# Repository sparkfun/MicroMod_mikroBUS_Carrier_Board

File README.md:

MicroMod mikroBUS™ Carrier Board
========================================

[*SparkFun MicroMod mikroBUS™ Carrier Board (DEV-18710)*](https://www.sparkfun.com/products/18710)

The SparkFun MicroMod mikroBUS Carrier Board takes advantage of the [MicroMod](https://www.sparkfun.com/micromod), [Qwiic](https://www.sparkfun.com/qwiic), and [mikroBUS™](https://www.mikroe.com/mikrobus) ecosystems and allows users to take advantage of the growing number of 7 [MicroMod processor boards](https://www.sparkfun.com/categories/tags/processor-board), 83 [Qwiic *(add-on)* boards](https://www.sparkfun.com/categories/tags/qwiic), and [1079 available](https://www.mikroe.com/click-boards) [Click boards™](https://www.sparkfun.com/categories/tags/click) *(as of September 2021)*, which equates to +51M different board combinations.

The mikroBUS socket comprises a pair of 8-pin female headers with a standardized pin configuration. The pins consist of three groups of communications pins (SPI, UART and I<sup>2</sup>C), six additional pins (PWM, Interrupt, Analog input, Reset and Chip select), and two power groups (3.3V and 5V).

_The [mikroBUS™ standard](https://www.mikroe.com/mikrobus) was developed by [MikroElektronika](https://www.mikroe.com/). Similar to our [Qwiic](https://www.sparkfun.com/qwiic) and [MicroMod](https://www.sparkfun.com/micromod) interfaces, mikroBUS™ provides a standardized connection for add-on [Click boards™](https://www.mikroe.com/click-boards) to be hooked up to a microcontroller based development board._

Repository Contents
-------------------

* **/Documentation** - Data sheets, additional product information
* **/Hardware** - Eagle design files (.brd, .sch)

Documentation
--------------

* **[Hookup Guide](https://learn.sparkfun.com/tutorials/2003)** - SparkFun MicroMod mikroBUS™ Carrier Board

Product Versions
----------------
* [DEV-18710](https://www.sparkfun.com/products/18710) -  initial release

License Information
-------------------

This product is _**open source**_! 

Please review the LICENSE.md file for license information. 

If you have any questions or concerns on licensing, please contact technical support on our [SparkFun forums](https://forum.sparkfun.com/viewforum.php?f=152).

Distributed as-is; no warranty is given.

- Your friends at SparkFun.

_<COLLABORATION CREDIT>_

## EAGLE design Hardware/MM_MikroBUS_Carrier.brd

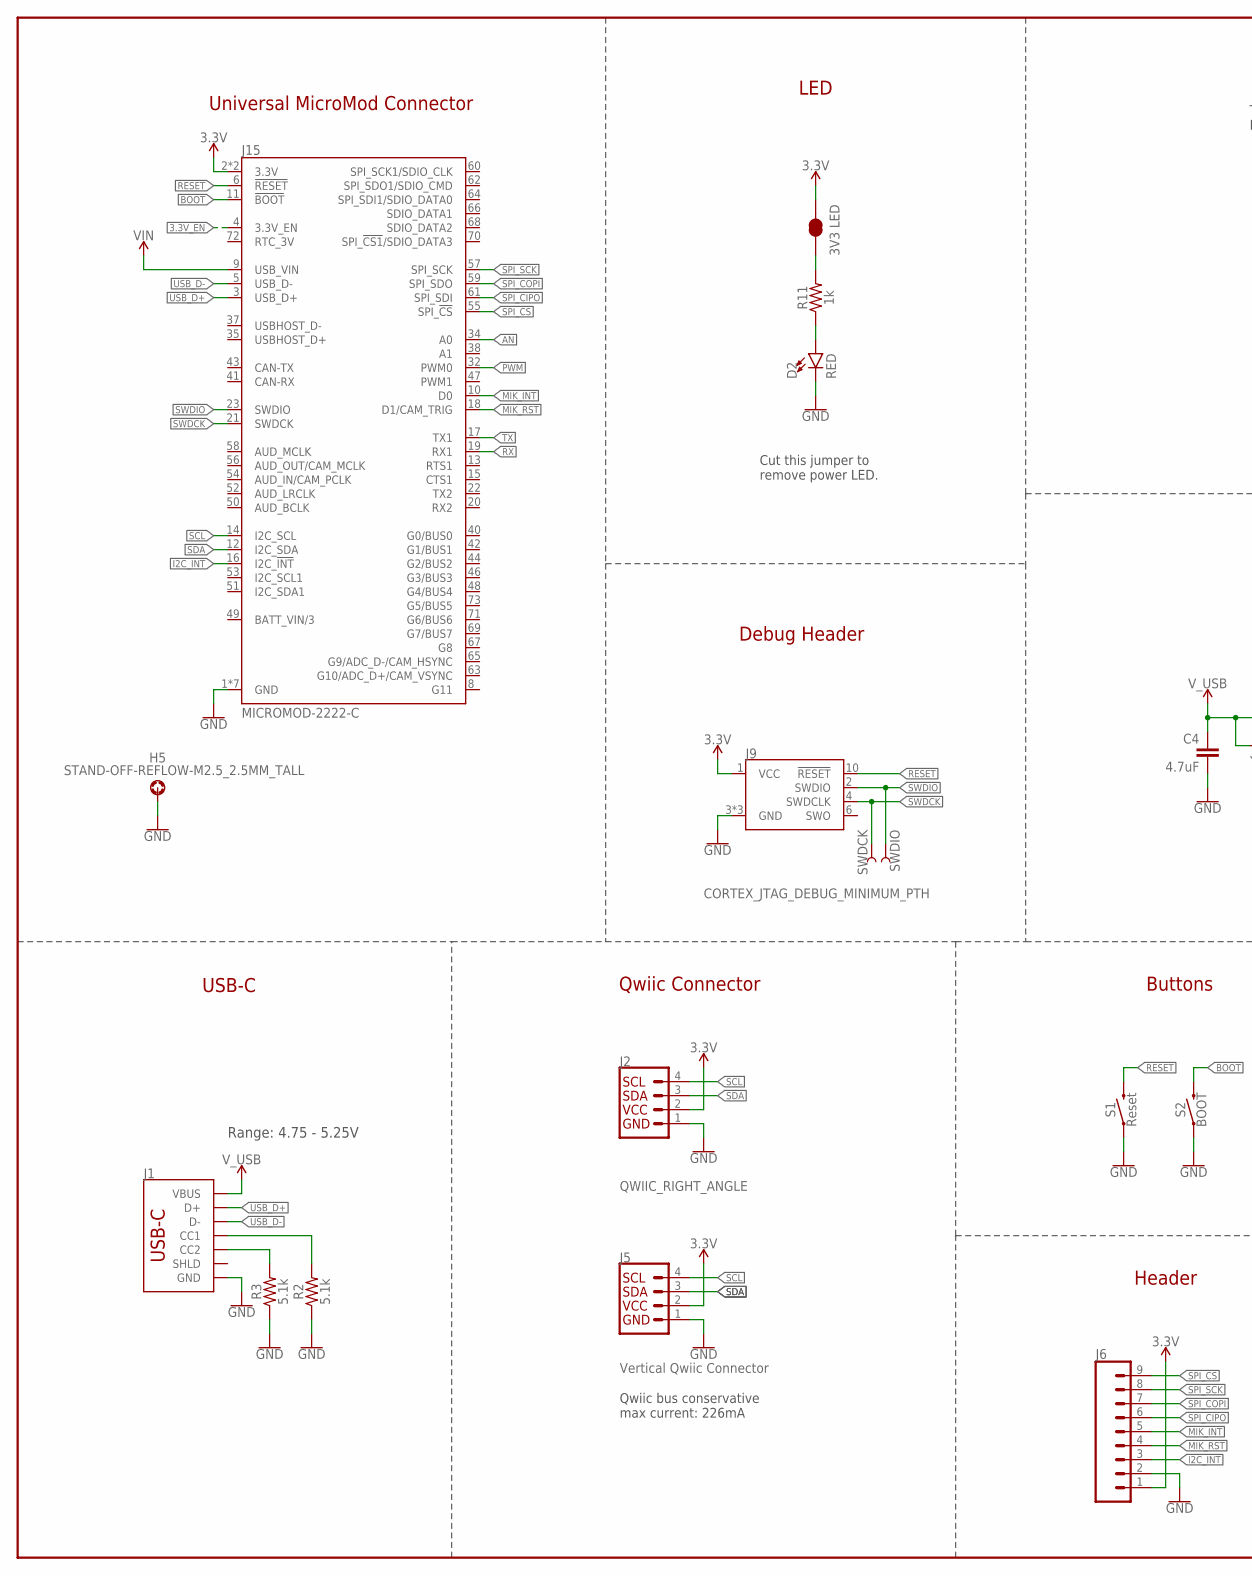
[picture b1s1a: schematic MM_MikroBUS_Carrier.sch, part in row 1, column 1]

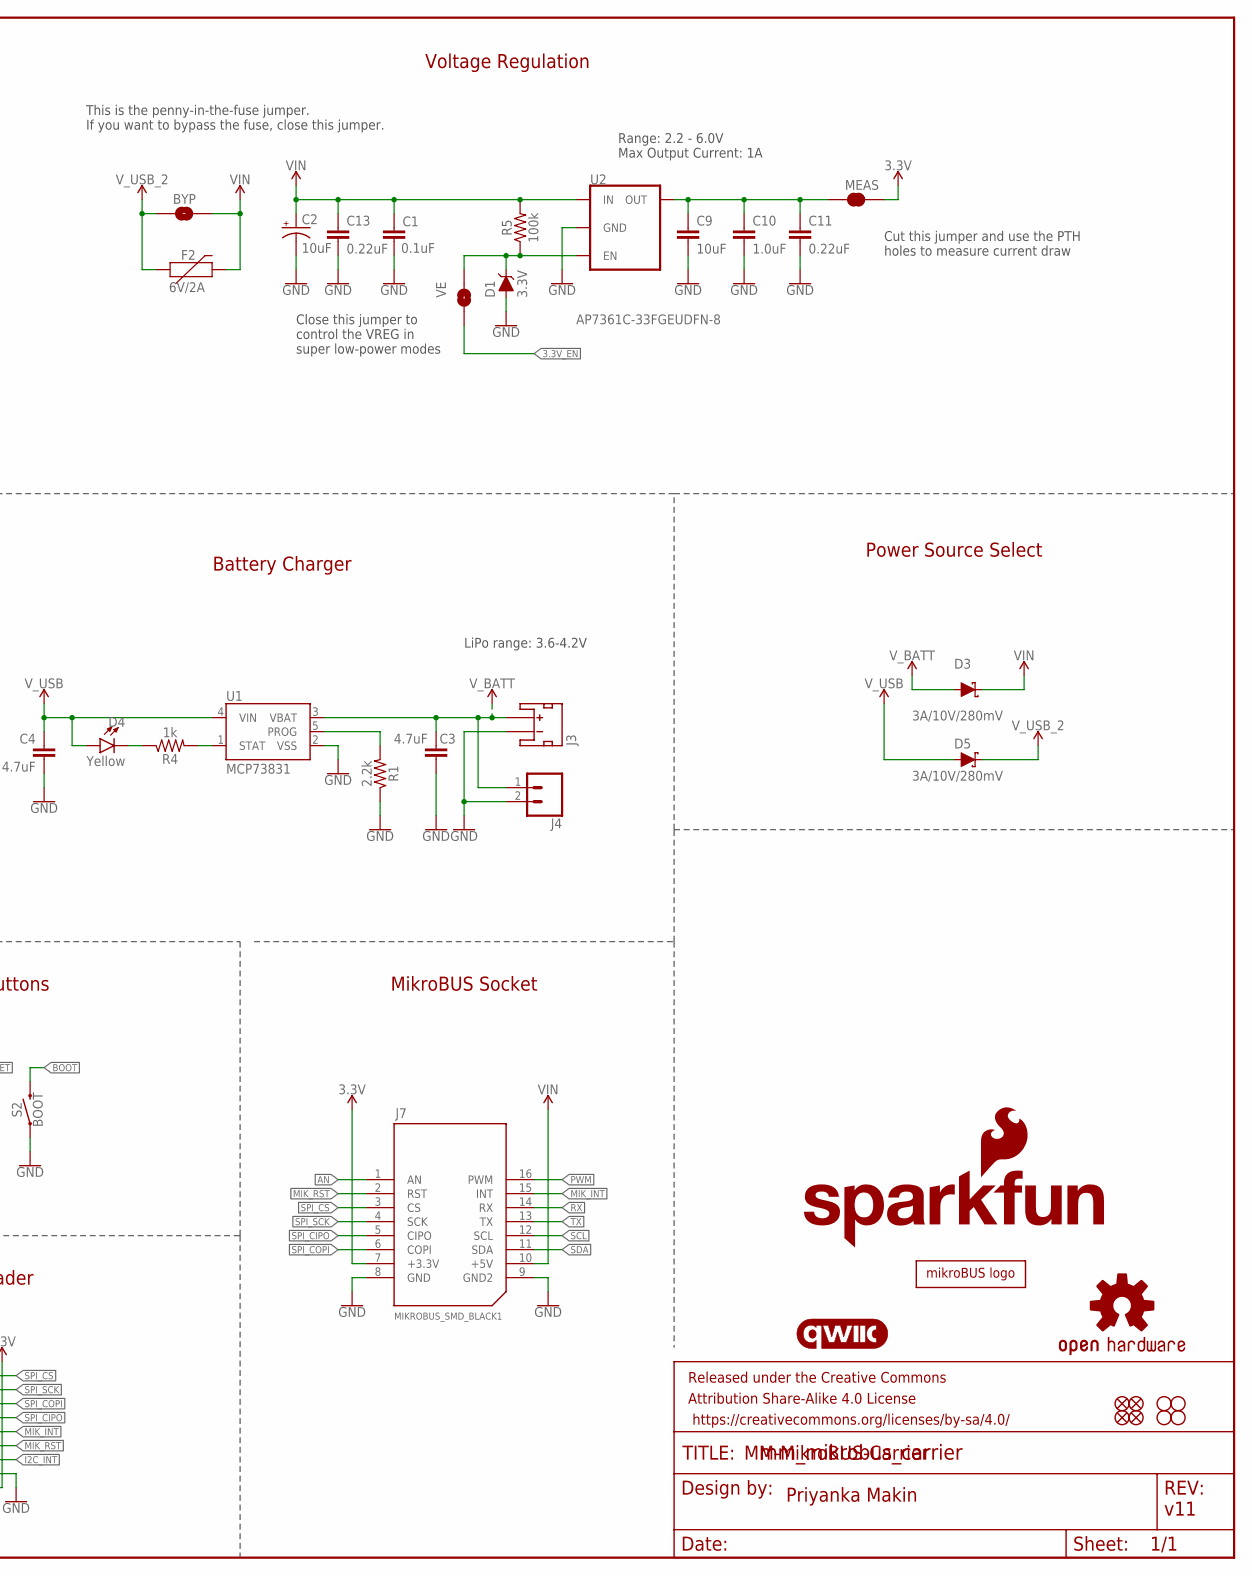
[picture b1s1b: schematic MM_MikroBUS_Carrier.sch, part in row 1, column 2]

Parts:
BYP: JUMPER-SMT_2_NO_SILK; SMT-JUMPER_2_NO_SILK
C1: 0.1uF; 0603
C2: 10uF; EIA3216
C3, C4: 4.7uF; 0603
C9: 10uF; 0603
C10: 1.0uF; 0603
C11, C13: 0.22uF; 0603
D1: 3.3V; SOD-323
D2: RED; LED-0603
D3, D5: 3A/10V/280mV; SOD-323
D4: Yellow; LED-0603
F2: 6V/2A; 1210
FD1, FD2, FD3, FD4: FIDUCIALUFIDUCIAL; FIDUCIAL-MICRO
FRAME1: FRAME-LEDGER; CREATIVE_COMMONS
H1, H2, H3, H4: STAND-OFF
H5: STAND-OFF-REFLOW-M2.5_2.5MM_TALL; STAND-OFF-REFLOW-M2.5
J1: USB_C_2-LAYER_PADS; USB-C-16P-2LAYER-PADS
J2: QWIIC_RIGHT_ANGLE; JST04_1MM_RA
J3: JST_2MM_MALE; JST-2-SMD
J4: CONN_021X02_NO_SILK; 1X02_NO_SILK
J5: Vertical Qwiic Connector; JST04_1MM_VERT
J6: CONN_09NO_SILK; 1X09_NO_SILK
J7: MIKROBUS_SMD_BLACK1; MIKROBUS_SMD_BLACK
J9: CORTEX_JTAG_DEBUG_MINIMUM_PTH; 2X5-PTH-1.27MM
J15: MICROMOD-2222-C; M.2-CONNECTOR-E
JP4: 3V3 LED; SMT-JUMPER_2_NC_TRACE_SILK
JP6: VE; SMT-JUMPER_2_NO_SILK
LOGO1: SFE_LOGO_NAME_FLAME.2_INCH; SFE_LOGO_NAME_FLAME_.2
LOGO2: QWIIC_LOGO_CONNECTOR; QWIIC_5.5MM
LOGO3: OSHW-LOGOM; OSHW-LOGO-M
MEAS: JUMPER-COMBO_2_NC_TRACE; COMBO-JUMPER_2_NC_TRACE
R1: 2.2k; 0603
R2, R3: 5.1k; 0603
R4, R11: 1k; 0603
R5: 100k; 0603
S1: Reset; TACTILE_SWITCH_SMD_5.2MM
S2: BOOT; TACTILE_SWITCH_SMD_5.2MM
SWDCK: TEST-POINTTP_15TH_THRU; TP_15TH
SWDIO: TEST-POINTTP_15TH_THRU; TP_15TH
U1: MCP73831; SOT23-5
U2: AP7361C-33FGEUDFN-8; UDFN-8
U$7: MIKROBUS_LOGO

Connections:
3.3V: J2.2, J5.2, J6.1, J7.7 (+3.3V), J9.1 (VCC), J15.2 (3.3V), J15.74 (3.3V), JP4.2, MEAS.2, MEAS.4 (2)
3.3V_EN: J15.4 (3.3V_EN), JP6.1
!BOOT!: J15.11 (!BOOT!), S2.3 (2), S2.4 (2)
!RESET!: J9.10 (!RESET), J15.6 (!RESET!), S1.3 (2), S1.4 (2)
AN: J7.1 (AN), J15.34 (A0)
GND: C1.2, C2.-, C3.2, C4.2, C9.2, C10.2, C11.2, C13.2, D1.A, D2.C, H5.1, J1.GND, J1.GND2 (GND), J2.1, J3.1 (-), J4.2, J5.1, J6.2, J7.8 (GND), J7.9 (GND2), J9.3 (GND), J9.5 (GND), J9.9 (GND), J15.1 (GND), J15.7 (GND), J15.33 (GND), J15.36 (GND), J15.39 (GND), J15.45 (GND), J15.75 (GND), R1.1, R2.1, R3.1, S1.1, S1.2 (1), S2.1, S2.2 (1), U1.2 (VSS), U2.4 (GND), U2.EP (GND)
I2C_!INT!: J6.3, J15.16 (I2C_!INT!)
MIK_INT: J6.5, J7.15 (INT), J15.10 (D0)
MIK_RST: J6.4, J7.2 (RST), J15.18 (D1/CAM_TRIG)
unnamed: C9.1, C10.1, C11.1, MEAS.1, MEAS.3 (1), U2.1 (OUT)
unnamed: R1.2, U1.5 (PROG)
unnamed: D4.C, R4.1
unnamed: JP4.1, R11.2
unnamed: D2.A, R11.1
unnamed: R4.2, U1.1 (STAT)
unnamed: J1.A5 (CC1), R2.2
unnamed: J1.B5 (CC2), R3.2
PWM: J7.16 (PWM), J15.32 (PWM0)
RX: J7.14 (RX), J15.19 (RX1)
SCL: J2.4, J5.4, J7.12 (SCL), J15.14 (I2C_SCL)
SDA: J2.3, J5.3, J7.11 (SDA), J15.12 (I2C_SDA)
SPI_!CS!: J6.9, J7.3 (CS), J15.55 (SPI_!CS!)
SPI_CIPO: J6.6, J7.5 (CIPO), J15.61 (SPI_SDI)
SPI_COPI: J6.7, J7.6 (COPI), J15.59 (SPI_SDO)
SPI_SCK: J6.8, J7.4 (SCK), J15.57 (SPI_SCK)
SWDCK: J9.4 (SWDCLK), J15.21 (SWDCK), SWDCK.1
SWDIO: J9.2 (SWDIO), J15.23 (SWDIO), SWDIO.1
TX: J7.13 (TX), J15.17 (TX1)
USB_D+: J1.A6 (D+), J1.B6 (D+), J15.3 (USB_D+)
USB_D-: J1.A7 (D-), J1.B7 (D-), J15.5 (USB_D-)
VIN: BYP.2, C1.1, C2.+, C13.1, D3.C, F2.2, J7.10 (+5V), J15.9 (USB_VIN), R5.2, U2.8 (IN)
VREG_EN: D1.C, JP6.2, R5.1, U2.5 (EN)
V_BATT: C3.1, D3.A, J3.2 (+), J4.1, U1.3 (VBAT)
V_USB: C4.1, D4.A, D5.A, J1.VBUS1 (VBUS), J1.VBUS2 (VBUS), U1.4 (VIN)
V_USB_2: BYP.1, D5.C, F2.1

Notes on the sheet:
USB-C
Universal MicroMod Connector
Priyanka Makin
MM-MikroBUS-Carrier
LED
v11
Cut this jumper to remove power LED.
Range: 4.75 - 5.25V
Voltage Regulation
Range: 2.2 - 6.0V Max Output Current: 1A
Close this jumper to control the VREG in super low-power modes
This is the penny-in-the-fuse jumper. If you want to bypass the fuse, close this jumper.
Qwiic Connector
Buttons
Battery Charger
Power Source Select
Qwiic bus conservative max current: 226mA
Header
Cut this jumper and use the PTH holes to measure current draw
LiPo range: 3.6-4.2V
MikroBUS Socket
Debug Header

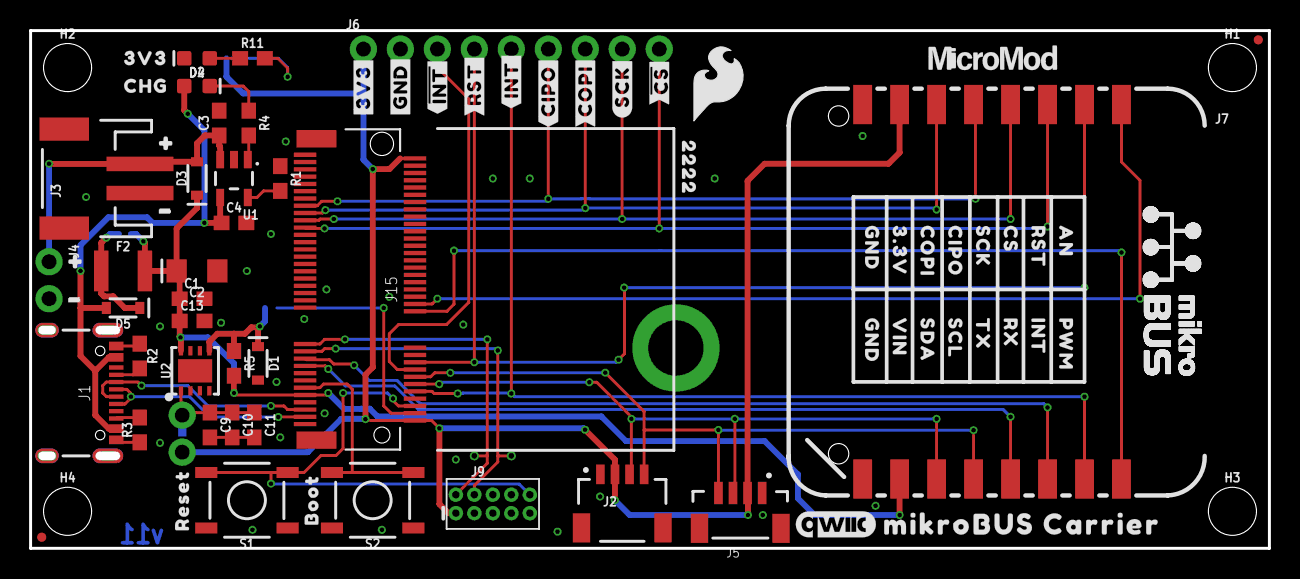
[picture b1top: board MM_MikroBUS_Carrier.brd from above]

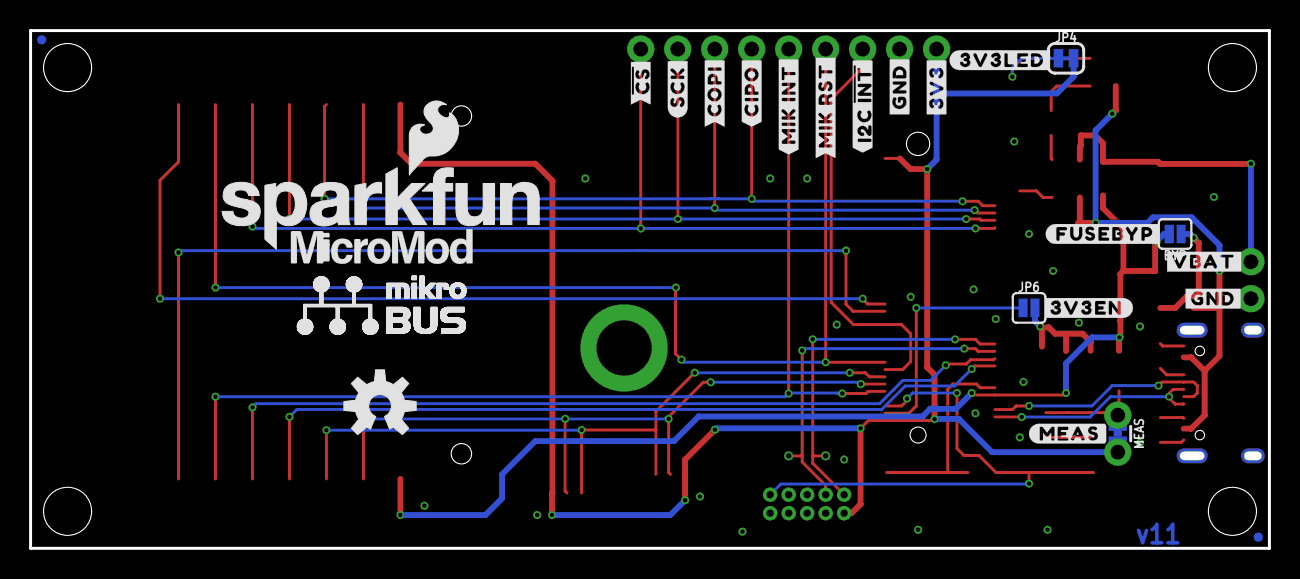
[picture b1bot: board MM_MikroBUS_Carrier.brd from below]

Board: 2 copper layers, 84.7 x 35.2 mm, 106 parts (25 on the bottom side), 35 nets.

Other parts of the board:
U$1: #3V3LED#0
U$2: MICROMOD_LOGO_.35
U$3: 3V30
U$4: CHG0
U$5: MIKROBUS_CARRIER0
U$6: #INT#0
U$8, U$14, U$33: #GND#0
U$9: #MEAS#0
U$10, U$13: #3V3#0
U$11, U$32, U$36, U$37: #0
U$12: #VBAT#0
U$15: ##INT##0
U$16: #MIK_INT#0
U$17: #RST#0
U$19: #MIK_RST#0
U$20: #I2C_#INT##0
U$22, U$23: #CIPO#0
U$24, U$25: #COPI#0
U$26, U$27: #SCK#0
U$28, U$29: ##CS##0
U$30: RESET0
U$31: BOOT0
U$34: 22220
U$35: AN0
U$38: #FUSEBYP#0
U$39: #3V3EN#0
U$40: RST0
U$41: CS0
U$42: SCK0
U$43: CIPO0
U$44: SFE_LOGO_FLAME_.2
U$45: COPI0
U$46: 3#3V0
U$47, U$48: GND0
U$49: PWM0
U$50: INT0
U$51: RX0
U$52: TX0
U$53: SCL0
U$54: SDA0
U$55: VIN0
U$68: MICROMOD_LOGO_.5

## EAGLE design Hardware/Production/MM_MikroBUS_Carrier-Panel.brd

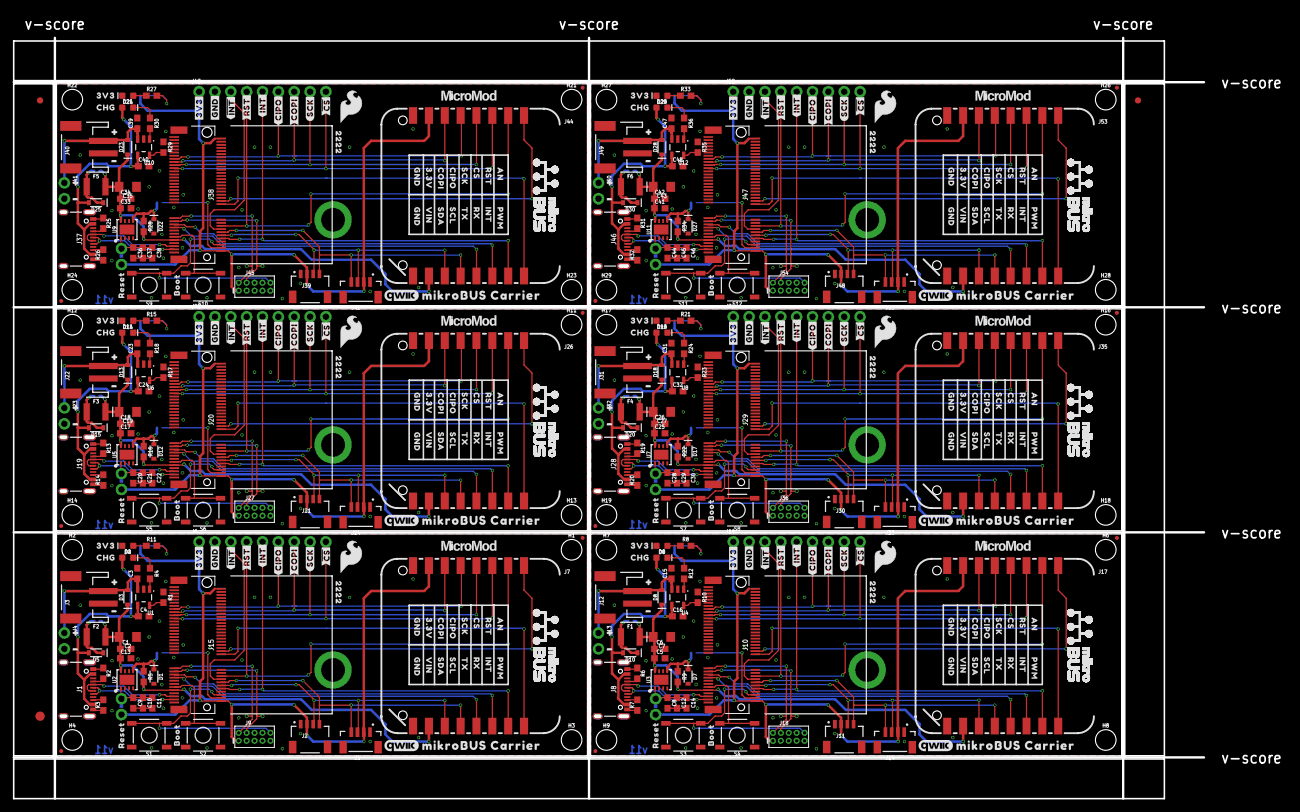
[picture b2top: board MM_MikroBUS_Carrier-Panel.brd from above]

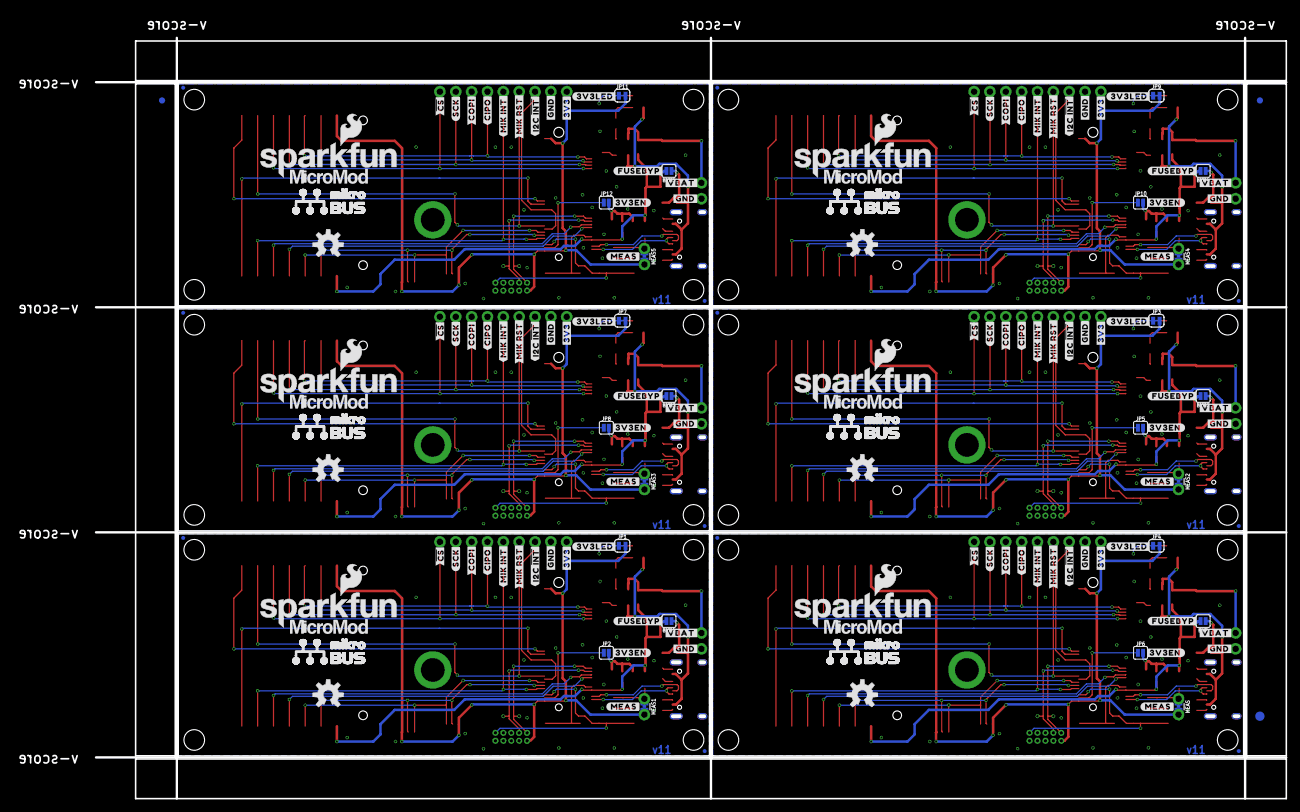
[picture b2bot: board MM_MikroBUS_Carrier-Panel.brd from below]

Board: 2 copper layers, 203.7 x 125.6 mm, 636 parts (153 on the bottom side), 210 nets.

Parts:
BYP, BYP1, BYP2, BYP3, BYP4, BYP5: JUMPER-SMT_2_NO_SILK; SMT-JUMPER_2_NO_SILK
C1, C6, C18, C26, C34, C42: 0.1uF; 0603
C2, C7, C19, C27, C35, C43: 10uF; EIA3216
C3, C4, C15, C16, C23, C24, C31, C32, C39, C40, C47, C48: 4.7uF; 0603
C5, C11, C13, C14, C17, C22, C25, C30, C33, C38, C41, C46: 0.22uF; 0603
C8, C9, C20, C28, C36, C44: 10uF; 0603
C10, C12, C21, C29, C37, C45: 1.0uF; 0603
D1, D7, D12, D17, D22, D27: 3.3V; SOD-323
D2, D6, D11, D16, D21, D26: RED; LED-0603
D3, D5, D8, D10, D13, D15, D18, D20, D23, D25, D28, D30: 3A/10V/280mV; SOD-323
D4, D9, D14, D19, D24, D29: Yellow; LED-0603
E$1, E$2, E$3, E$4: FIDUCIAL-1X2
E$5, E$6: FIDUCIAL-1.5X3
F1, F2, F3, F4, F5, F6: 6V/2A; 1210
FD1, FD2, FD3, FD4, FD5, FD6, FD7, FD8, FD9, FD10, FD11, FD12, FD13, FD14, FD15, FD16, FD17, FD18, FD19, FD20, FD21, FD22, FD23, FD24: FIDUCIALUFIDUCIAL; FIDUCIAL-MICRO
H1, H2, H3, H4, H6, H7, H8, H9, H11, H12, H13, H14, H16, H17, H18, H19, H21, H22, H23, H24, H26, H27, H28, H29: STAND-OFF
H5, H10, H15, H20, H25, H30: STAND-OFF-REFLOW-M2.5_2.5MM_TALL; STAND-OFF-REFLOW-M2.5
J1, J8, J19, J28, J37, J46: USB-C-16P-2LAYER-PADS
J2, J11, J21, J30, J39, J48: QWIIC_RIGHT_ANGLE; JST04_1MM_RA
J3, J12, J22, J31, J40, J49: JST-2-SMD
J4, J13, J23, J32, J41, J50: 1X02_NO_SILK
J5, J14, J24, J33, J42, J51: Vertical Qwiic Connector; JST04_1MM_VERT
J6, J16, J25, J34, J43, J52: 1X09_NO_SILK
J7, J17, J26, J35, J44, J53: MIKROBUS_SMD_BLACK1; MIKROBUS_SMD_BLACK
J9, J18, J27, J36, J45, J54: CORTEX_JTAG_DEBUG_MINIMUM_PTH; 2X5-PTH-1.27MM
J10, J15, J20, J29, J38, J47: MICROMOD-2222-C; M.2-CONNECTOR-E
JP1, JP3, JP4, JP7, JP9, JP11: 3V3 LED; SMT-JUMPER_2_NC_TRACE_SILK
JP2, JP5, JP6, JP8, JP10, JP12: VE; SMT-JUMPER_2_NO_SILK
LOGO1, LOGO6, LOGO9, LOGO12, LOGO15, LOGO18: SFE_LOGO_NAME_FLAME.2_INCH; SFE_LOGO_NAME_FLAME_.2
LOGO2, LOGO4, LOGO7, LOGO10, LOGO13, LOGO16: QWIIC_LOGO_CONNECTOR; QWIIC_5.5MM
LOGO3, LOGO5, LOGO8, LOGO11, LOGO14, LOGO17: OSHW-LOGOM; OSHW-LOGO-M
MEAS, MEAS1, MEAS2, MEAS3, MEAS4, MEAS5: JUMPER-COMBO_2_NC_TRACE; COMBO-JUMPER_2_NC_TRACE
R1, R10, R17, R23, R29, R35: 2.2k; 0603
R2, R3, R6, R7, R13, R14, R19, R20, R25, R26, R31, R32: 5.1k; 0603
R4, R8, R11, R12, R15, R18, R21, R24, R27, R30, R33, R36: 1k; 0603
R5, R9, R16, R22, R28, R34: 100k; 0603
S1, S3, S5, S7, S9, S11: Reset; TACTILE_SWITCH_SMD_5.2MM
S2, S4, S6, S8, S10, S12: BOOT; TACTILE_SWITCH_SMD_5.2MM
SWDCK, SWDCK1, SWDCK2, SWDCK3, SWDCK4, SWDCK5: TEST-POINTTP_15TH_THRU; TP_15TH
SWDIO, SWDIO1, SWDIO2, SWDIO3, SWDIO4, SWDIO5: TEST-POINTTP_15TH_THRU; TP_15TH
U1, U4, U6, U8, U10, U12: MCP73831; SOT23-5
U2, U3, U5, U7, U9, U11: AP7361C-33FGEUDFN-8; UDFN-8
U$1, U$100, U$154, U$208, U$262, U$316: #3V3LED#0
U$2, U$80, U$134, U$188, U$242, U$296: MICROMOD_LOGO_.35
U$3, U$58, U$113, U$167, U$221, U$275: 3V30
U$4, U$56, U$111, U$165, U$219, U$273: CHG0
U$5, U$83, U$137, U$191, U$245, U$299: MIKROBUS_CARRIER0
U$6, U$104, U$158, U$212, U$266, U$320: #INT#0
U$7, U$101, U$155, U$209, U$263, U$317: MIKROBUS_LOGO
U$8, U$14, U$33, U$59, U$60, U$69, U$114, U$115, U$123, U$168, U$169, U$177, U$222, U$223, U$231, U$276, U$277, U$285: #GND#0
U$9, U$57, U$112, U$166, U$220, U$274: #MEAS#0
U$10, U$13, U$81, U$82, U$135, U$136, U$189, U$190, U$243, U$244, U$297, U$298: #3V3#0
U$11, U$32, U$36, U$37, U$70, U$71, U$72, U$73, U$124, U$125, U$126, U$127, U$178, U$179, U$180, U$181, U$232, U$233, U$234, U$235, U$286, U$287, U$288, U$289: #0
U$12, U$67, U$122, U$176, U$230, U$284: #VBAT#0
U$15, U$79, U$133, U$187, U$241, U$295: ##INT##0
U$16, U$107, U$161, U$215, U$269, U$323: #MIK_INT#0
U$17, U$105, U$159, U$213, U$267, U$321: #RST#0
U$18, U$44, U$109, U$163, U$217, U$271: SFE_LOGO_FLAME_.2
U$19, U$108, U$162, U$216, U$270, U$324: #MIK_RST#0
U$20, U$106, U$160, U$214, U$268, U$322: #I2C_#INT##0
U$21, U$68, U$110, U$164, U$218, U$272: MICROMOD_LOGO_.5
U$22, U$23, U$61, U$62, U$116, U$117, U$170, U$171, U$224, U$225, U$278, U$279: #CIPO#0
U$24, U$25, U$63, U$64, U$118, U$119, U$172, U$173, U$226, U$227, U$280, U$281: #COPI#0
U$26, U$27, U$65, U$66, U$120, U$121, U$174, U$175, U$228, U$229, U$282, U$283: #SCK#0
U$28, U$29, U$77, U$78, U$131, U$132, U$185, U$186, U$239, U$240, U$293, U$294: ##CS##0
U$30, U$74, U$128, U$182, U$236, U$290: RESET0
U$31, U$75, U$129, U$183, U$237, U$291: BOOT0
U$34, U$76, U$130, U$184, U$238, U$292: 22220
U$35, U$84, U$138, U$192, U$246, U$300: AN0
U$38, U$102, U$156, U$210, U$264, U$318: #FUSEBYP#0
U$39, U$103, U$157, U$211, U$265, U$319: #3V3EN#0
U$40, U$85, U$139, U$193, U$247, U$301: RST0
U$41, U$86, U$140, U$194, U$248, U$302: CS0
U$42, U$87, U$141, U$195, U$249, U$303: SCK0
U$43, U$88, U$142, U$196, U$250, U$304: CIPO0
U$45, U$89, U$143, U$197, U$251, U$305: COPI0
U$46, U$90, U$144, U$198, U$252, U$306: 3#3V0
U$47, U$48, U$91, U$92, U$145, U$146, U$199, U$200, U$253, U$254, U$307, U$308: GND0
U$49, U$93, U$147, U$201, U$255, U$309: PWM0
U$50, U$94, U$148, U$202, U$256, U$310: INT0
U$51, U$95, U$149, U$203, U$257, U$311: RX0
U$52, U$96, U$150, U$204, U$258, U$312: TX0
U$53, U$97, U$151, U$205, U$259, U$313: SCL0
U$54, U$98, U$152, U$206, U$260, U$314: SDA0
U$55, U$99, U$153, U$207, U$261, U$315: VIN0

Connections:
3.3V: J2.2, J5.2, J6.1, J7.7, J9.1, J15.2, J15.74, JP4.2, MEAS.2, MEAS.4
3.3V1: J10.2, J10.74, J11.2, J14.2, J16.1, J17.7, J18.1, JP1.2, MEAS1.2, MEAS1.4
3.3V2: J20.2, J20.74, J21.2, J24.2, J25.1, J26.7, J27.1, JP3.2, MEAS2.2, MEAS2.4
3.3V3: J29.2, J29.74, J30.2, J33.2, J34.1, J35.7, J36.1, JP7.2, MEAS3.2, MEAS3.4
3.3V4: J38.2, J38.74, J39.2, J42.2, J43.1, J44.7, J45.1, JP9.2, MEAS4.2, MEAS4.4
3.3V5: J47.2, J47.74, J48.2, J51.2, J52.1, J53.7, J54.1, JP11.2, MEAS5.2, MEAS5.4
3.3V_EN: J15.4, JP6.1
3.3V_EN1: J10.4, JP2.1
3.3V_EN2: J20.4, JP5.1
3.3V_EN3: J29.4, JP8.1
3.3V_EN4: J38.4, JP10.1
3.3V_EN5: J47.4, JP12.1
!BOOT!: J15.11, S2.3, S2.4
!BOOT!1: J10.11, S4.3, S4.4
!BOOT!2: J20.11, S6.3, S6.4
!BOOT!3: J29.11, S8.3, S8.4
!BOOT!4: J38.11, S10.3, S10.4
!BOOT!5: J47.11, S12.3, S12.4
!RESET!: J9.10, J15.6, S1.3, S1.4
!RESET!1: J10.6, J18.10, S3.3, S3.4
!RESET!2: J20.6, J27.10, S5.3, S5.4
!RESET!3: J29.6, J36.10, S7.3, S7.4
!RESET!4: J38.6, J45.10, S9.3, S9.4
!RESET!5: J47.6, J54.10, S11.3, S11.4
AN: J7.1, J15.34
AN1: J10.34, J17.1
AN2: J20.34, J26.1
AN3: J29.34, J35.1
AN4: J38.34, J44.1
AN5: J47.34, J53.1
GND: C1.2, C2.-, C3.2, C4.2, C9.2, C10.2, C11.2, C13.2, D1.A, D2.C, H5.1, J1.GND, J1.GND2, J2.1, J3.1, J4.2, J5.1, J6.2, J7.8, J7.9, J9.3, J9.5, J9.9, J15.1, J15.7, J15.33, J15.36, J15.39, J15.45, J15.75, R1.1, R2.1, R3.1, S1.1, S1.2, S2.1, S2.2, U1.2, U2.4, U2.EP
GND1: C5.2, C6.2, C7.-, C8.2, C12.2, C14.2, C15.2, C16.2, D6.C, D7.A, H10.1, J8.GND, J8.GND2, J10.1, J10.7, J10.33, J10.36, J10.39, J10.45, J10.75, J11.1, J12.1, J13.2, J14.1, J16.2, J17.8, J17.9, J18.3, J18.5, J18.9, R6.1, R7.1, R10.1, S3.1, S3.2, S4.1, S4.2, U3.4, U3.EP, U4.2
GND2: C17.2, C18.2, C19.-, C20.2, C21.2, C22.2, C23.2, C24.2, D11.C, D12.A, H15.1, J19.GND, J19.GND2, J20.1, J20.7, J20.33, J20.36, J20.39, J20.45, J20.75, J21.1, J22.1, J23.2, J24.1, J25.2, J26.8, J26.9, J27.3, J27.5, J27.9, R13.1, R14.1, R17.1, S5.1, S5.2, S6.1, S6.2, U5.4, U5.EP, U6.2
GND3: C25.2, C26.2, C27.-, C28.2, C29.2, C30.2, C31.2, C32.2, D16.C, D17.A, H20.1, J28.GND, J28.GND2, J29.1, J29.7, J29.33, J29.36, J29.39, J29.45, J29.75, J30.1, J31.1, J32.2, J33.1, J34.2, J35.8, J35.9, J36.3, J36.5, J36.9, R19.1, R20.1, R23.1, S7.1, S7.2, S8.1, S8.2, U7.4, U7.EP, U8.2
GND4: C33.2, C34.2, C35.-, C36.2, C37.2, C38.2, C39.2, C40.2, D21.C, D22.A, H25.1, J37.GND, J37.GND2, J38.1, J38.7, J38.33, J38.36, J38.39, J38.45, J38.75, J39.1, J40.1, J41.2, J42.1, J43.2, J44.8, J44.9, J45.3, J45.5, J45.9, R25.1, R26.1, R29.1, S9.1, S9.2, S10.1, S10.2, U9.4, U9.EP, U10.2
GND5: C41.2, C42.2, C43.-, C44.2, C45.2, C46.2, C47.2, C48.2, D26.C, D27.A, H30.1, J46.GND, J46.GND2, J47.1, J47.7, J47.33, J47.36, J47.39, J47.45, J47.75, J48.1, J49.1, J50.2, J51.1, J52.2, J53.8, J53.9, J54.3, J54.5, J54.9, R31.1, R32.1, R35.1, S11.1, S11.2, S12.1, S12.2, U11.4, U11.EP, U12.2
I2C_!INT!: J6.3, J15.16
I2C_!INT!1: J10.16, J16.3
I2C_!INT!2: J20.16, J25.3
I2C_!INT!3: J29.16, J34.3
I2C_!INT!4: J38.16, J43.3
I2C_!INT!5: J47.16, J52.3
MIK_INT: J6.5, J7.15, J15.10
MIK_INT1: J10.10, J16.5, J17.15
MIK_INT2: J20.10, J25.5, J26.15
MIK_INT3: J29.10, J34.5, J35.15
MIK_INT4: J38.10, J43.5, J44.15
MIK_INT5: J47.10, J52.5, J53.15
MIK_RST: J6.4, J7.2, J15.18
MIK_RST1: J10.18, J16.4, J17.2
MIK_RST2: J20.18, J25.4, J26.2
MIK_RST3: J29.18, J34.4, J35.2
MIK_RST4: J38.18, J43.4, J44.2
MIK_RST5: J47.18, J52.4, J53.2
unnamed: C9.1, C10.1, C11.1, MEAS.1, MEAS.3, U2.1
unnamed: R1.2, U1.5
unnamed: D4.C, R4.1
unnamed: JP4.1, R11.2
unnamed: J8.A5, R6.2
unnamed: D2.A, R11.1
unnamed: J8.B5, R7.2
unnamed: R4.2, U1.1
unnamed: JP1.1, R8.2
unnamed: J1.A5, R2.2
unnamed: J1.B5, R3.2
unnamed: D6.A, R8.1
unnamed: C8.1, C12.1, C14.1, MEAS1.1, MEAS1.3, U3.1
unnamed: R10.2, U4.5
unnamed: D9.C, R12.1
unnamed: R12.2, U4.1
unnamed: J19.A5, R13.2
unnamed: J19.B5, R14.2
unnamed: JP3.1, R15.2
unnamed: D11.A, R15.1
unnamed: C20.1, C21.1, C22.1, MEAS2.1, MEAS2.3, U5.1
unnamed: R17.2, U6.5
unnamed: D14.C, R18.1
unnamed: R18.2, U6.1
unnamed: J28.A5, R19.2
unnamed: J28.B5, R20.2
unnamed: JP7.1, R21.2
unnamed: D16.A, R21.1
unnamed: C28.1, C29.1, C30.1, MEAS3.1, MEAS3.3, U7.1
unnamed: R23.2, U8.5
unnamed: D19.C, R24.1
unnamed: R24.2, U8.1
unnamed: J37.A5, R25.2
unnamed: J37.B5, R26.2
unnamed: JP9.1, R27.2
unnamed: D21.A, R27.1
unnamed: C36.1, C37.1, C38.1, MEAS4.1, MEAS4.3, U9.1
unnamed: R29.2, U10.5
unnamed: D24.C, R30.1
unnamed: R30.2, U10.1
unnamed: J46.A5, R31.2
unnamed: J46.B5, R32.2
unnamed: JP11.1, R33.2
unnamed: D26.A, R33.1
unnamed: C44.1, C45.1, C46.1, MEAS5.1, MEAS5.3, U11.1
unnamed: R35.2, U12.5
unnamed: D29.C, R36.1
unnamed: R36.2, U12.1
PWM: J7.16, J15.32
PWM1: J10.32, J17.16
PWM2: J20.32, J26.16
PWM3: J29.32, J35.16
PWM4: J38.32, J44.16
PWM5: J47.32, J53.16
RX: J7.14, J15.19
RX1: J10.19, J17.14
RX2: J20.19, J26.14
RX3: J29.19, J35.14
RX4: J38.19, J44.14
RX5: J47.19, J53.14
SCL: J2.4, J5.4, J7.12, J15.14
SCL1: J10.14, J11.4, J14.4, J17.12
SCL2: J20.14, J21.4, J24.4, J26.12
SCL3: J29.14, J30.4, J33.4, J35.12
SCL4: J38.14, J39.4, J42.4, J44.12
SCL5: J47.14, J48.4, J51.4, J53.12
SDA: J2.3, J5.3, J7.11, J15.12
SDA1: J10.12, J11.3, J14.3, J17.11
SDA2: J20.12, J21.3, J24.3, J26.11
SDA3: J29.12, J30.3, J33.3, J35.11
SDA4: J38.12, J39.3, J42.3, J44.11
SDA5: J47.12, J48.3, J51.3, J53.11
SPI_!CS!: J6.9, J7.3, J15.55
SPI_!CS!1: J10.55, J16.9, J17.3
SPI_!CS!2: J20.55, J25.9, J26.3
SPI_!CS!3: J29.55, J34.9, J35.3
SPI_!CS!4: J38.55, J43.9, J44.3
SPI_!CS!5: J47.55, J52.9, J53.3
SPI_CIPO: J6.6, J7.5, J15.61
SPI_CIPO1: J10.61, J16.6, J17.5
SPI_CIPO2: J20.61, J25.6, J26.5
SPI_CIPO3: J29.61, J34.6, J35.5
SPI_CIPO4: J38.61, J43.6, J44.5
SPI_CIPO5: J47.61, J52.6, J53.5
SPI_COPI: J6.7, J7.6, J15.59
SPI_COPI1: J10.59, J16.7, J17.6
SPI_COPI2: J20.59, J25.7, J26.6
SPI_COPI3: J29.59, J34.7, J35.6
SPI_COPI4: J38.59, J43.7, J44.6
SPI_COPI5: J47.59, J52.7, J53.6
SPI_SCK: J6.8, J7.4, J15.57
SPI_SCK1: J10.57, J16.8, J17.4
SPI_SCK2: J20.57, J25.8, J26.4
SPI_SCK3: J29.57, J34.8, J35.4
SPI_SCK4: J38.57, J43.8, J44.4
SPI_SCK5: J47.57, J52.8, J53.4
SWDCK: J9.4, J15.21, SWDCK.1
SWDCK1: J10.21, J18.4, SWDCK1.1
SWDCK2: J20.21, J27.4, SWDCK2.1
SWDCK3: J29.21, J36.4, SWDCK3.1
SWDCK4: J38.21, J45.4, SWDCK4.1
SWDCK5: J47.21, J54.4, SWDCK5.1
SWDIO: J9.2, J15.23, SWDIO.1
SWDIO1: J10.23, J18.2, SWDIO1.1
SWDIO2: J20.23, J27.2, SWDIO2.1
SWDIO3: J29.23, J36.2, SWDIO3.1
SWDIO4: J38.23, J45.2, SWDIO4.1
SWDIO5: J47.23, J54.2, SWDIO5.1
TX: J7.13, J15.17
TX1: J10.17, J17.13
TX2: J20.17, J26.13
TX3: J29.17, J35.13
TX4: J38.17, J44.13
TX5: J47.17, J53.13
USB_D+: J1.A6, J1.B6, J15.3
USB_D+1: J8.A6, J8.B6, J10.3
USB_D+2: J19.A6, J19.B6, J20.3
USB_D+3: J28.A6, J28.B6, J29.3
USB_D+4: J37.A6, J37.B6, J38.3
USB_D+5: J46.A6, J46.B6, J47.3
USB_D-: J1.A7, J1.B7, J15.5
USB_D-1: J8.A7, J8.B7, J10.5
USB_D-2: J19.A7, J19.B7, J20.5
USB_D-3: J28.A7, J28.B7, J29.5
USB_D-4: J37.A7, J37.B7, J38.5
USB_D-5: J46.A7, J46.B7, J47.5
VIN: BYP.2, C1.1, C2.+, C13.1, D3.C, F2.2, J7.10, J15.9, R5.2, U2.8
VIN1: BYP1.2, C5.1, C6.1, C7.+, D8.C, F1.2, J10.9, J17.10, R9.2, U3.8
VIN2: BYP2.2, C17.1, C18.1, C19.+, D13.C, F3.2, J20.9, J26.10, R16.2, U5.8
VIN3: BYP3.2, C25.1, C26.1, C27.+, D18.C, F4.2, J29.9, J35.10, R22.2, U7.8
VIN4: BYP4.2, C33.1, C34.1, C35.+, D23.C, F5.2, J38.9, J44.10, R28.2, U9.8
VIN5: BYP5.2, C41.1, C42.1, C43.+, D28.C, F6.2, J47.9, J53.10, R34.2, U11.8
VREG_EN: D1.C, JP6.2, R5.1, U2.5
VREG_EN1: D7.C, JP2.2, R9.1, U3.5
VREG_EN2: D12.C, JP5.2, R16.1, U5.5
VREG_EN3: D17.C, JP8.2, R22.1, U7.5
VREG_EN4: D22.C, JP10.2, R28.1, U9.5
VREG_EN5: D27.C, JP12.2, R34.1, U11.5
V_BATT: C3.1, D3.A, J3.2, J4.1, U1.3
V_BATT1: C15.1, D8.A, J12.2, J13.1, U4.3
V_BATT2: C23.1, D13.A, J22.2, J23.1, U6.3
V_BATT3: C31.1, D18.A, J31.2, J32.1, U8.3
V_BATT4: C39.1, D23.A, J40.2, J41.1, U10.3
V_BATT5: C47.1, D28.A, J49.2, J50.1, U12.3
V_USB: C4.1, D4.A, D5.A, J1.VBUS1, J1.VBUS2, U1.4
V_USB1: C16.1, D9.A, D10.A, J8.VBUS1, J8.VBUS2, U4.4
V_USB2: C24.1, D14.A, D15.A, J19.VBUS1, J19.VBUS2, U6.4
V_USB3: C32.1, D19.A, D20.A, J28.VBUS1, J28.VBUS2, U8.4
V_USB4: C40.1, D24.A, D25.A, J37.VBUS1, J37.VBUS2, U10.4
V_USB5: C48.1, D29.A, D30.A, J46.VBUS1, J46.VBUS2, U12.4
V_USB_1: BYP1.1, D10.C, F1.1
V_USB_2: BYP.1, D5.C, F2.1
V_USB_3: BYP2.1, D15.C, F3.1
V_USB_4: BYP3.1, D20.C, F4.1
V_USB_5: BYP4.1, D25.C, F5.1
V_USB_6: BYP5.1, D30.C, F6.1

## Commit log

2021-09-14 Initial commit
    Starting with the MicroMod Qwiic Carrier - Single files.
2021-09-14 Renamed eagle files
2021-09-16 Working on proto
2021-09-16 Finished proto design
2021-09-20 Updates from proto design review
    MikroBUS device:
    * add pin numbers back into sch symbol
    * label with a "J" prefix
    * Center anchor/origin
    * Remove internal pin labels
    Schematic:
2021-09-21 Proto checklist
    Updated silkscreen and measures
2021-09-21 Update schematic
2021-09-22 Approve errors
2021-09-23 Add prod-id to mikroBUS socket
2021-09-23 Update name and value of mikroBUS socket and generate gerbers
2021-10-28 Add HW test sketch
2021-10-28 Updating with mikroE suggestions
    * "mikroBUS" label, not "MikroBUS"
    * Add pin names to socket
    * Change button labeling to "Mikroe Reset"
2021-10-29 Rename bord.h folder
2021-11-10 Updates to board.h file
2021-12-01 MikroE updates
    * Add JTAG connector
    * Remove mikroE reset button
    * Moved mikroBUS labels so that they can all be seen when socket is populated
2021-12-01 Pete's updates
    * Bump version number on schematic and board
    * Add measures for header
    * Add test points for SWDIO and SWDCK
2021-12-01 Pete's updates:
    * LED jumper label became "3V3LED"
    * fuse jumper label became "FUSE_BYP"
2021-12-02 Design review updates:
    * Put mikroBUS pin labels into the table
    * Add y-measure for mikroBUS socket
    * Add mikroBUS logo to library and to the back of the board
    * Add GND vias
2021-12-02 Design review updates
    * Add direction to the SPI header labels
    * Remove underscores from labels
2021-12-02 QC double-check
2021-12-03 Add more measures
2021-12-03 Panelize and generate gerbers
2021-12-03 Create zip of eagle files
2022-01-10 Fixed test sketches
2022-01-21 v11 - switch RX and TX to match mikroBUS standard.
2022-01-21 Re-panelize and generate new gerbers for v11
2022-01-25 Update MM_MikroBUS_Carrier.brd
    Add dimensions
2022-01-25 Update MM_MikroBUS_Carrier.brd
    Move text to clear measurements areas

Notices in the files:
parts and their libraries:
SparkFun-Aesthetics: Licensing: Creative Commons ShareAlike 4.0 International - https://creativecommons.org/licenses/by-sa/4.0
SparkFun-Aesthetics: Released under the Creative Commons Attribution Share-Alike 4.0 License
SparkFun-Aesthetics: https://creativecommons.org/licenses/by-sa/4.0
